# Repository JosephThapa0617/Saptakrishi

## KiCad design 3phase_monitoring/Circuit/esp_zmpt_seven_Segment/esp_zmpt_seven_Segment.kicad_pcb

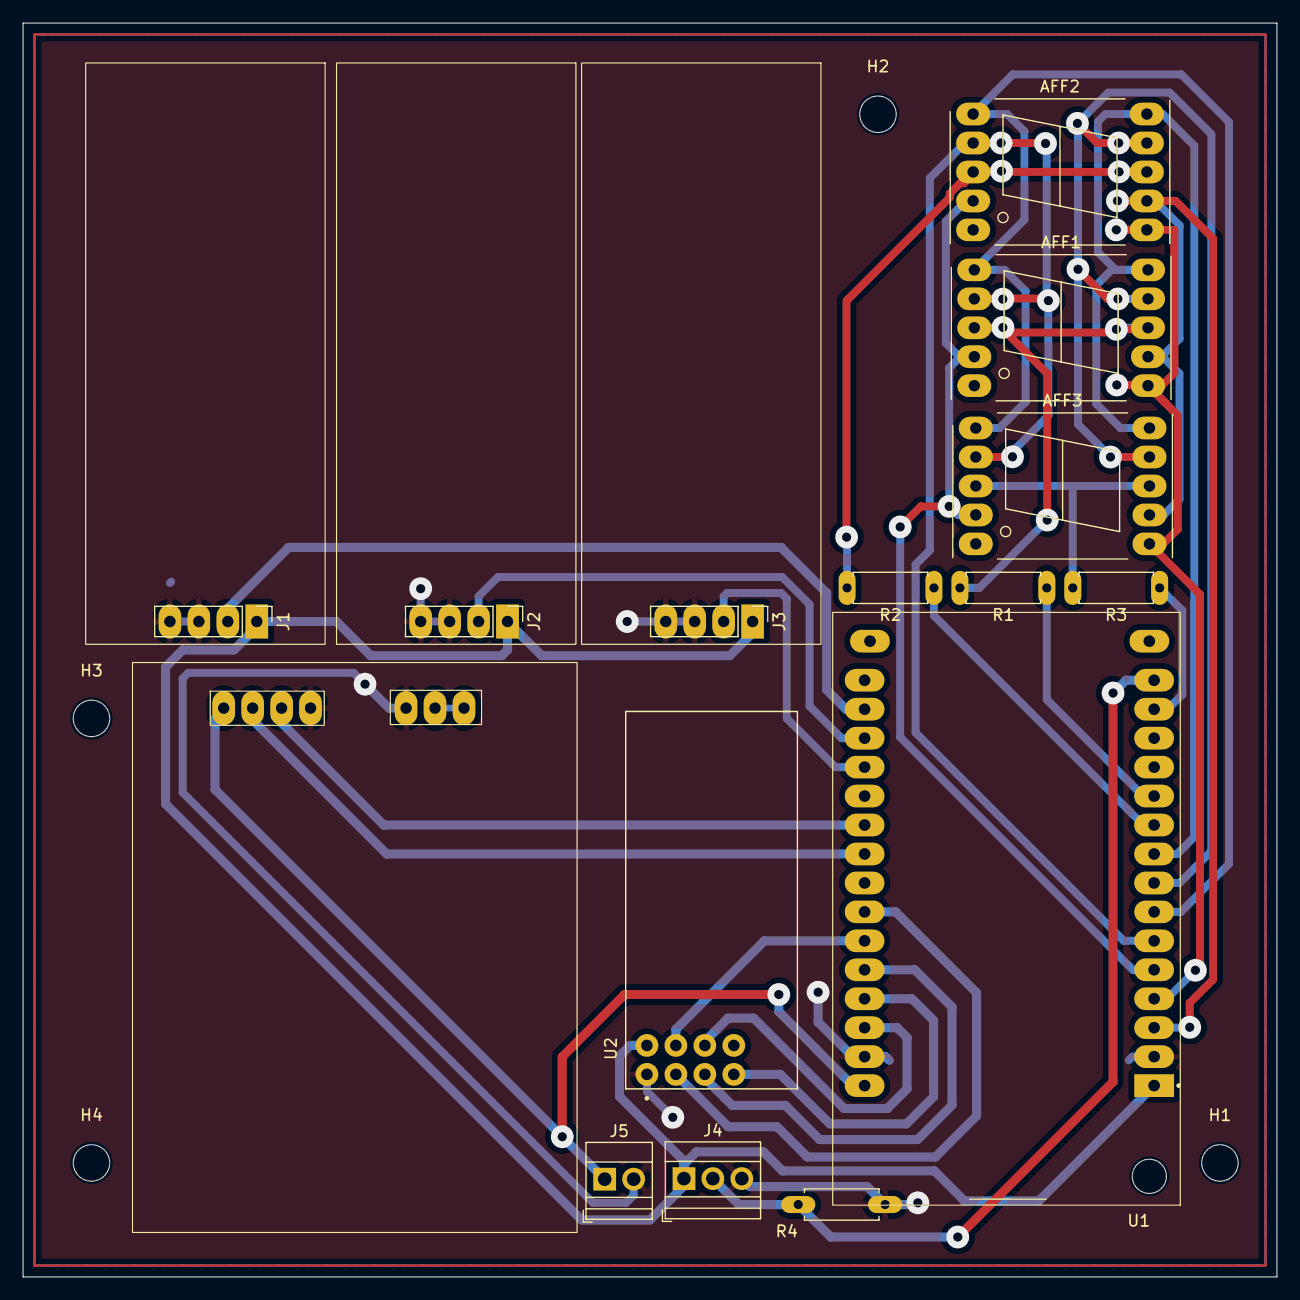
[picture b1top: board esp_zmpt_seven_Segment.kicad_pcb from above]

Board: 2 copper layers, 110.0 x 110.0 mm, 19 parts (0 on the bottom side), 28 nets.

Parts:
AFF1, AFF2, AFF3: LTS-6960HR; 7SegmentLED_LTS6760_LTS6780
H1, H2, H3, H4: MountingHole; MountingHole_3.2mm_M3
J1, J2, J3: Conn_01x04_Pin; zmpt101b
J4: Screw_Terminal_01x03; TerminalBlock_Xinya_XY308-2.54-3P_1x03_P2.54mm_Horizontal
J5: Screw_Terminal_01x02; TerminalBlock_Xinya_XY308-2.54-2P_1x02_P2.54mm_Horizontal
J6: Conn_01x07_Pin; double channel relay
R1, R2, R3: R; R_Axial_DIN0207_L6.3mm_D2.5mm_P7.62mm_Horizontal
R4: 4.7K; R_Axial_DIN0207_L6.3mm_D2.5mm_P7.62mm_Horizontal
U1: ESP32-DEVKIT-V1; ESP32
U2: NRF24L01P-MODULE-PCB; XCVR_NRF24L01P-MODULE-PCB

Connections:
+5V: J5.1, J6.1, U1.30 (VIN)
/3V3: J1.1, J2.1, J3.1, J4.1, U1.1 (3V3), U2.2 (VDD)
/AnalogRead1: J1.2, U1.17 (VP)
/AnalogRead2: J2.2, U1.18 (VN)
/AnalogRead3: J3.2, U1.19 (D34)
/C.A.1: AFF2.3 (C.A.), AFF2.8 (C.A.), R2.2
/C.A.2: AFF1.3 (C.A.), AFF1.8 (C.A.), R1.2
/C.A.3: AFF3.3 (C.A.), AFF3.8 (C.A.), R3.2
/C.E.: U1.24 (D26), U2.3 (CE)
/CSN: U1.25 (D27), U2.4 (~CSN)
/DS18b20: J4.2, R4.1, U1.15 (D23)
/JDVCC: J6.6, J6.7
/MISO: U1.27 (D12), U2.7 (MISO)
/MOSI: U1.28 (D13), U2.6 (MOSI)
/S.CK: U1.26 (D14), U2.5 (SCK)
/a: AFF1.7 (a), AFF2.7 (a), AFF3.7 (a), U1.3 (D15)
/b: AFF1.6 (b), AFF2.6 (b), AFF3.6 (b), U1.4 (D2)
/c: AFF1.4 (c), AFF2.4 (c), AFF3.4 (c), U1.5 (D4)
/compressor: J6.2, U1.22 (D33)
/d: AFF1.2 (d), AFF2.2 (d), AFF3.2 (d), U1.6 (RX2)
/defrost: J6.3, U1.21 (D32)
/e: AFF1.1 (e), AFF2.1 (e), AFF3.1 (e), U1.7 (TX2)
/f: AFF1.9 (f), AFF2.9 (f), AFF3.9 (f), U1.8 (D5)
/g: AFF1.10 (g), AFF2.10 (g), AFF3.10 (g), U1.9 (D18)
/ones: R3.1, U1.14 (D22)
/sign: R2.1, U1.10 (D19)
/tens: R1.1, U1.11 (D21)
GND: J1.3, J1.4, J2.3, J2.4, J3.3, J3.4, J4.3, J5.2, J6.4, J6.5, R4.2, U1.2 (GND), U1.29 (GND), U2.1 (GND)
